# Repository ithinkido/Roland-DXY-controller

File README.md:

# Roland-DXY-controller
 A modern ESP32 based controller for Roland DXY plotter with i2c shift regisers for button mapping, OLED dispay, solenoid drivers and on board TMC silent stepper drivers 

 Two boards have been designed. 
 ## [TMC 2208](https://github.com/ithinkido/Roland-DXY-controller/tree/TMC-2208)
 Standard STEP/DIR  control no UART
 ## [TMC 2209](https://github.com/ithinkido/Roland-DXY-controller/tree/TMC-2209)
  UAURT + STEP/DIR control with posiblity to use stall guard and all other features of UART controlled TMC

  **See branches for more info**

The board is designed to be a a plug in replacemnt with NO modifications to the existing plotter hardware.

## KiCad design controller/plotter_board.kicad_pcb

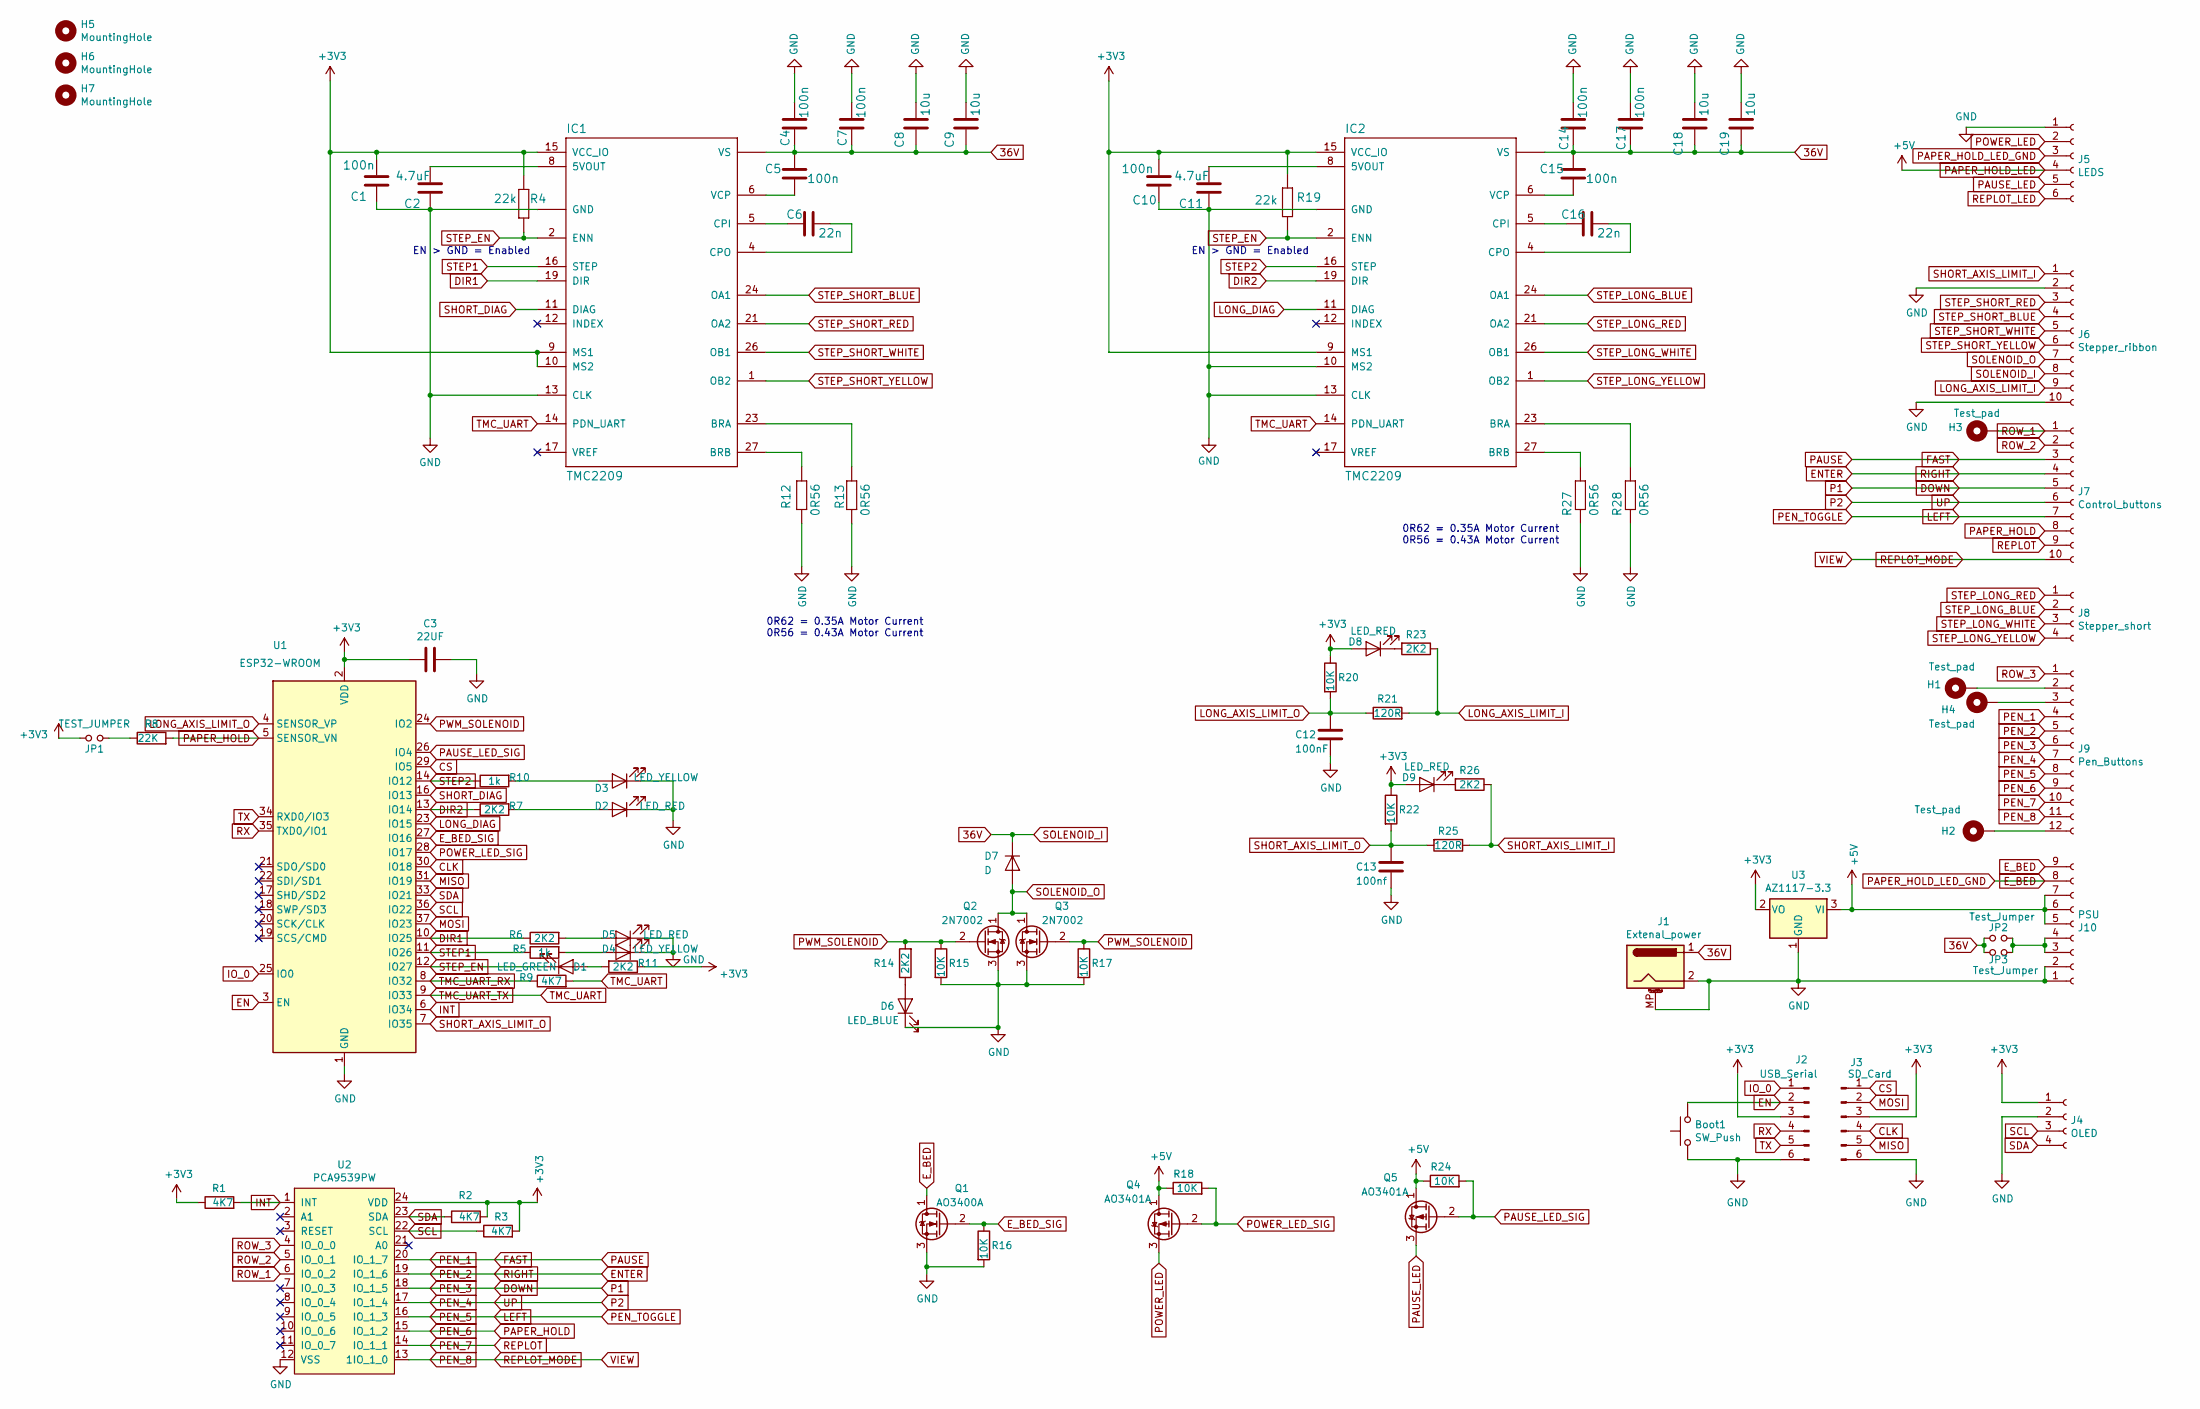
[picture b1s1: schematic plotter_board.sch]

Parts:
Boot1: SW_Push; SW_Tactile_SPST_Angled_PTS645Vx58-2LFS
C1, C5, C10, C15: 100n; C_0402_1005Metric; LCSC C1525
C2, C11: 4.7uF; C_0402_1005Metric; LCSC C23733
C3: 22UF; C_0603_1608Metric; LCSC C59461
C4, C7, C14, C17: 100n; C_0603_1608Metric; LCSC C14663
C6, C16: 22n; C_0402_1005Metric; LCSC C1532
C8, C9, C18, C19: 10u; C_1206_3216Metric; LCSC C13585
C12: 100nF; C_0402_1005Metric; LCSC C1525
C13: 100nf; C_0402_1005Metric; LCSC C1525
D1: LED_GREEN; LED_0603_1608Metric; LCSC C72043
D2, D5, D8, D9: LED_RED; LED_0603_1608Metric; LCSC C2286
D3, D4: LED_YELLOW; LED_0603_1608Metric; LCSC C72038
D6: LED_BLUE; LED_0603_1608Metric; LCSC C72041
D7: D; D_SOD-123F; LCSC C64898
H1, H2, H3, H4: Test_pad; PinHeader_1x01_P2.54mm_Vertical
H5, H6, H7: MountingHole; MountingHole_3.7mm_Pad_Via
IC1, IC2: TMC2209; TMC2209-LA; LCSC C465949
J1: Extenal_power; BarrelJack_Wuerth_6941xx301002
J2: USB_Serial; PinSocket_1x06_P2.54mm_Vertical
J3: SD_Card; PinSocket_1x06_P2.54mm_Vertical
J4: OLED; PinHeader_1x04_P2.54mm_Vertical
J5: LEDS; Molex_SPOX_5267-06A_1x06_P2.50mm_Vertical
J6: Stepper_ribbon; Ribbon_1.25mm_FFC_10pin
J7: Control_buttons; Molex_SPOX_5267-10A_1x10_P2.50mm_Vertical
J8: Stepper_short; PinHeader_1x04_P2.00mm_Vertical
J9: Pen_Buttons; Molex_SPOX_5267-12A_1x12_P2.50mm_Vertical
J10: PSU; Molex_SPOX_5267-09A_1x09_P2.50mm_Vertical
JP1: TEST_JUMPER; SolderJumper-2_P1.3mm_Open_RoundedPad1.0x1.5mm
JP2, JP3: Test_Jumper; SolderJumper-2_P1.3mm_Open_RoundedPad1.0x1.5mm
Q1: AO3400A; SOT-23; LCSC C20917
Q2, Q3: 2N7002; SOT-23; LCSC C8545
Q4, Q5: AO3401A; SOT-23; LCSC C15127
R1: 4K7; R_0402_1005Metric; LCSC C25744
R2, R3, R9: 4K7; R_0402_1005Metric; LCSC C25900
R4, R19: 22k; R_0402_1005Metric; LCSC C25768
R5, R10: 1k; R_0603_1608Metric; LCSC C21190
R6, R7, R11, R14, R23, R26: 2K2; R_0603_1608Metric; LCSC C4190
R8: 22K; R_0402_1005Metric; LCSC C25768
R12, R13, R27, R28: 0R56; R_1206_3216Metric; LCSC C104949
R15, R16, R17, R18, R20, R22, R24: 10K; R_0402_1005Metric; LCSC C25744
R21, R25: 120R; R_0402_1005Metric; LCSC C25079
U1: ESP32-WROOM; ESP32-WROOM-32; LCSC C473012
U2: PCA9539PW; TSSOP-24_4.4x7.8mm_P0.65mm; LCSC C129516
U3: AZ1117-3.3; SOT-223-3_TabPin2

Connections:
36V: C4.1, C5.1, C7.1, C8.1, C9.1, C14.1, C15.1, C17.1, C18.1, C19.1, D7.1 (K), IC1.22 (VS), IC1.28 (VS), IC2.22 (VS), IC2.28 (VS), J1.1, J6.8, JP2.1, JP3.1
+3V3: C1.2, C3.2, C10.2, D8.2 (A), D9.2 (A), IC1.9 (MS1), IC1.10 (MS2), IC1.15 (VCC_IO), IC2.9 (MS1), IC2.15 (VCC_IO), J2.3, J3.3, J4.1, JP1.2, R1.1, R2.2, R3.2, R4.1, R11.1, R19.1, R20.1, R22.1, U1.2 (VDD), U2.24 (VDD), U3.2 (VO)
CLK: J3.4, U1.30 (IO18)
CS: J3.1, U1.29 (IO5)
DIR1: IC1.19 (DIR), R6.1, U1.10 (IO25)
DIR2: IC2.19 (DIR), R7.1, U1.13 (IO14)
DOWN: J7.5, J9.6, U2.18 (IO_1_5)
EN: Boot1.2, J2.2, U1.3 (EN)
ENTER: J7.4, J9.5, U2.19 (IO_1_6)
E_BED: J5.3, J10.8, J10.9, Q1.1 (D)
E_BED_SIG: Q1.2 (G), R16.1, U1.27 (IO16)
FAST: J7.3, J9.4, U2.20 (IO_1_7)
GND: Boot1.1, C1.1, C2.1, C3.1, C4.2, C7.2, C8.2, C9.2, C10.1, C11.1, C12.2, C13.2, C14.2, C17.2, C18.2, C19.2, D2.1 (K), D3.1 (K), D4.1 (K), D5.1 (K), D6.1 (K), IC1.3 (GND), IC1.13 (CLK), IC1.18 (GND), IC1.29, IC1.TP (GND), IC2.3 (GND), IC2.10 (MS2), IC2.13 (CLK), IC2.18 (GND), IC2.29, IC2.TP (GND), J1.2, J1.MP (MountPin), J2.6, J3.6, J4.2, J5.1, J6.2, J6.10, J10.1, J10.2, Q1.3 (S), Q2.3 (S), Q3.3 (S), R12.1, R13.1, R15.2, R16.2, R17.2, R27.1, R28.1, U1.1 (GND), U1.15 (GND), U1.38 (GND), U1.39 (GND), U2.12 (VSS), U3.1 (GND)
INT: R1.2, U1.6 (IO34), U2.1 (INT)
IO_0: J2.1, U1.25 (IO0)
LEFT: J7.7, J9.8, U2.16 (IO_1_3)
LONG_AXIS_LIMIT_I: J6.9, R21.2, R23.1
LONG_AXIS_LIMIT_O: C12.1, R20.2, R21.1, U1.4 (SENSOR_VP)
LONG_DIAG: IC2.11 (DIAG), U1.23 (IO15)
MISO: J3.5, U1.31 (IO19)
MOSI: J3.2, U1.37 (IO23)
unnamed: C2.2, IC1.8 (5VOUT)
unnamed: C5.2, IC1.6 (VCP)
unnamed: C6.1, IC1.5 (CPI)
unnamed: C6.2, IC1.4 (CPO)
unnamed: C11.2, IC2.8 (5VOUT)
unnamed: C15.2, IC2.6 (VCP)
unnamed: C16.1, IC2.5 (CPI)
unnamed: C16.2, IC2.4 (CPO)
unnamed: D1.2 (A), R11.2
unnamed: D2.2 (A), R7.2
unnamed: D3.2 (A), R10.2
unnamed: D4.2 (A), R5.2
unnamed: D5.2 (A), R6.2
unnamed: D6.2 (A), R14.1
unnamed: D8.1 (K), R23.2
unnamed: D9.1 (K), R26.2
unnamed: H1.1, J9.2
unnamed: H2.1, J9.12
unnamed: H4.1, J9.3
unnamed: IC1.23 (BRA), R13.2
unnamed: IC1.27 (BRB), R12.2
unnamed: IC2.23 (BRA), R28.2
unnamed: IC2.27 (BRB), R27.2
unnamed: J10.3, J10.4, JP2.2, JP3.2
unnamed: JP1.1, R8.1
P2: J7.6, J9.7, U2.17 (IO_1_4)
PAPER_HOLD: J7.8, J9.9, R8.2, U1.5 (SENSOR_VN), U2.15 (IO_1_2)
PAPER_HOLD_LED: J5.4, J10.5, J10.6, J10.7, Q4.1 (D), Q5.1 (D), R18.1, R24.1, U3.3 (VI)
PAUSE_LED: J5.5, Q5.3 (S)
PAUSE_LED_SIG: Q5.2 (G), R24.2, U1.26 (IO4)
PEN_7: J7.9, J9.10, U2.14 (IO_1_1)
PEN_8: J7.10, J9.11, U2.13 (1IO_1_0)
POWER_LED: J5.2, Q4.3 (S)
POWER_LED_SIG: Q4.2 (G), R18.2, U1.28 (IO17)
PWM_SOLENOID: Q2.2 (G), Q3.2 (G), R14.2, R15.1, R17.1, U1.24 (IO2)
REPLOT_LED: J5.6
ROW_1: H3.1, J7.1, U2.6 (IO_0_2)
ROW_2: J7.2, U2.5 (IO_0_1)
ROW_3: J9.1, U2.4 (IO_0_0)
RX: J2.4, U1.35 (TXD0/IO1)
SCL: J4.3, R3.1, U1.36 (IO22), U2.22 (SCL)
SDA: J4.4, R2.1, U1.33 (IO21), U2.23 (SDA)
SHORT_AXIS_LIMIT_I: J6.1, R25.1, R26.1
SHORT_AXIS_LIMIT_O: C13.1, R22.2, R25.2, U1.7 (IO35)
SHORT_DIAG: IC1.11 (DIAG), U1.16 (IO13)
SOLENOID_O: D7.2 (A), J6.7, Q2.1 (D), Q3.1 (D)
STEP1: IC1.16 (STEP), R5.1, U1.11 (IO26)
STEP2: IC2.16 (STEP), R10.1, U1.14 (IO12)
STEP_EN: D1.1 (K), IC1.2 (ENN), IC2.2 (ENN), R4.2, R19.2, U1.12 (IO27)
STEP_LONG_BLUE: IC2.24 (OA1), J8.2
STEP_LONG_RED: IC2.21 (OA2), J8.1
STEP_LONG_WHITE: IC2.26 (OB1), J8.3
STEP_LONG_YELLOW: IC2.1 (OB2), J8.4
STEP_SHORT_BLUE: IC1.24 (OA1), J6.4
STEP_SHORT_RED: IC1.21 (OA2), J6.3
STEP_SHORT_WHITE: IC1.26 (OB1), J6.5
STEP_SHORT_YELLOW: IC1.1 (OB2), J6.6
TMC_UART: IC1.14 (PDN_UART), IC2.14 (PDN_UART), R9.2, U1.9 (IO33)
TMC_UART_RX: R9.1, U1.8 (IO32)
TX: J2.5, U1.34 (RXD0/IO3)

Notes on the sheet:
EN > GND = Enabled
0R62 = 0.35A Motor Current 0R56 = 0.43A Motor Current

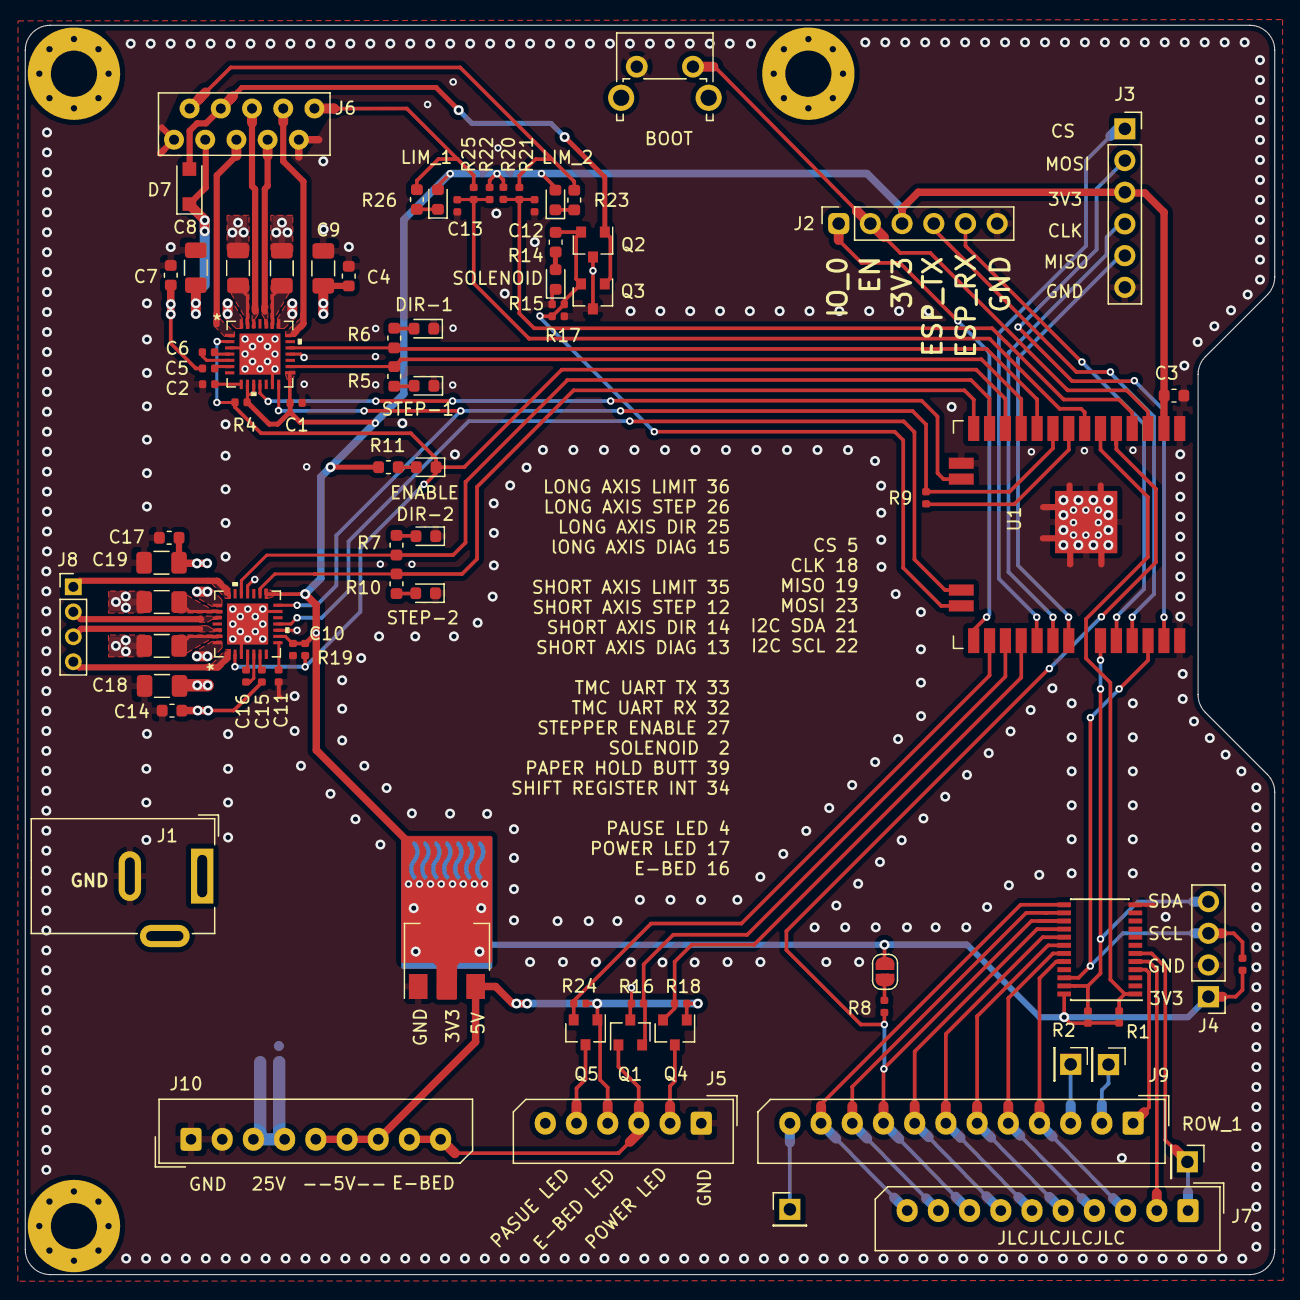
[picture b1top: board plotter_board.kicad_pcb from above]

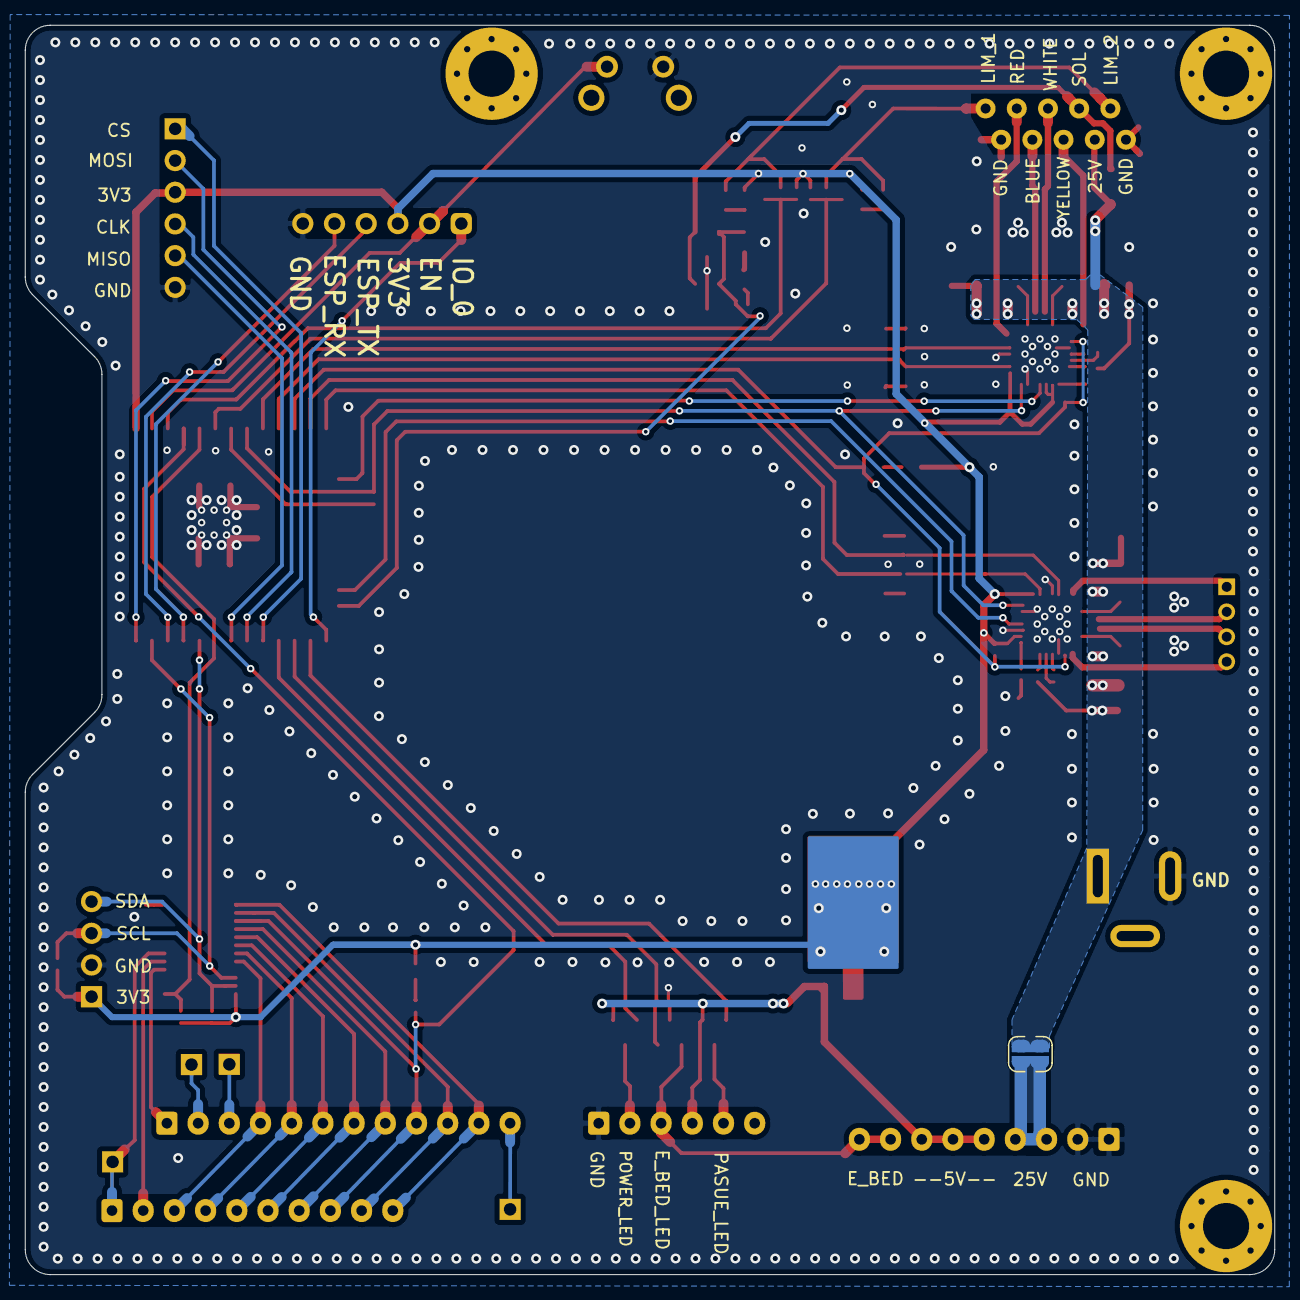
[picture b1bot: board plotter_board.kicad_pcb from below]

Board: 2 copper layers, 100.1 x 100.1 mm, 88 parts (3 on the bottom side), 80 nets.

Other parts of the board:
svg2mod: G***; pad_all

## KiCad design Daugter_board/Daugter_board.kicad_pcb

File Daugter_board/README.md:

This board takes care of the USB-C serial comms as well as the SD card. It is piggybacked onto the main board to postion the connectors correctly within the case openings.

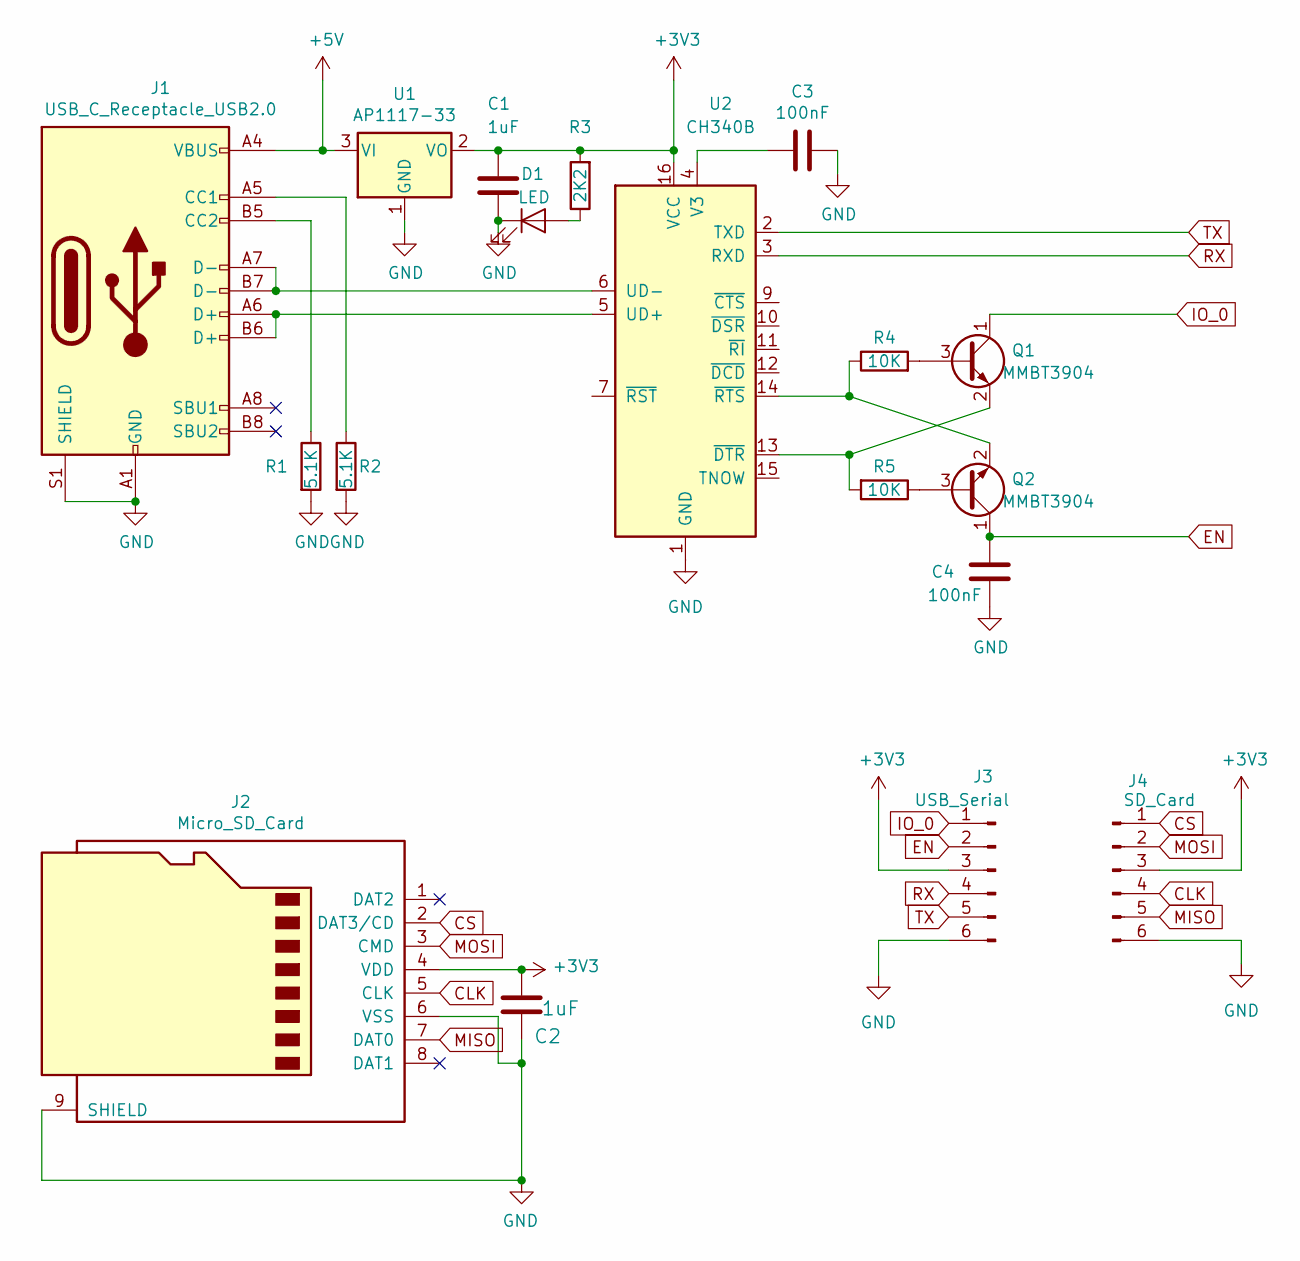
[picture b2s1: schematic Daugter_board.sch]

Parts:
C1: 1uF; C_0402_1005Metric; LCSC C52923
C2: 1uF; C_0805_2012Metric; LCSC C28323
C3, C4: 100nF; C_0402_1005Metric; LCSC C1525
D1: LED; LED_0603_1608Metric; LCSC C72041
J1: USB_C_Receptacle_USB2.0; USB_C_Receptacle_HRO_TYPE-C-31-M-12; LCSC C165948
J2: Micro_SD_Card; Conn_uSDcard; LCSC C111196
J3: USB_Serial; PinSocket_1x06_P2.54mm_Vertical
J4: SD_Card; PinSocket_1x06_P2.54mm_Vertical
Q1, Q2: MMBT3904; SOT-23; LCSC C20526
R1, R2: 5.1K; R_0402_1005Metric; LCSC C25905
R3: 2K2; R_0603_1608Metric; LCSC C4190
R4, R5: 10K; R_0402_1005Metric; LCSC C25744
U1: AP1117-33; SOT-223-3_TabPin2; LCSC C6186
U2: CH340B; SOIC-16_3.9x9.9mm_P1.27mm; LCSC C81010

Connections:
+3V3: C1.1, C2.2, J2.4 (VDD), J3.3, J4.3, R3.2, U1.2 (VO), U2.16 (VCC)
+5V: J1.A4 (VBUS), J1.A9 (VBUS), J1.B4 (VBUS), J1.B9 (VBUS), U1.3 (VI)
CLK: J2.5 (CLK), J4.4
CS: J2.2 (DAT3/CD), J4.1
EN: C4.2, J3.2, Q2.1 (C)
GND: C1.2, C2.1, C3.1, C4.1, D1.1 (K), J1.A1 (GND), J1.A12 (GND), J1.B1 (GND), J1.B12 (GND), J1.S1 (SHIELD), J2.6 (VSS), J2.9 (SHIELD), J3.6, J4.6, R1.2, R2.2, U1.1 (GND), U2.1 (GND)
IO_0: J3.1, Q1.1 (C)
MISO: J2.7 (DAT0), J4.5
MOSI: J2.3 (CMD), J4.2
unnamed: C3.2, U2.4 (V3)
unnamed: D1.2 (A), R3.1
unnamed: J1.A5 (CC1), R2.1
unnamed: J1.A6 (D+), J1.B6 (D+), U2.5 (UD+)
unnamed: J1.A7 (D-), J1.B7 (D-), U2.6 (UD-)
unnamed: J1.B5 (CC2), R1.1
unnamed: Q1.2 (E), R5.2, U2.13 (~DTR)
unnamed: Q1.3 (B), R4.2
unnamed: Q2.2 (E), R4.1, U2.14 (~RTS)
unnamed: Q2.3 (B), R5.1
RX: J3.4, U2.3 (RXD)
TX: J3.5, U2.2 (TXD)

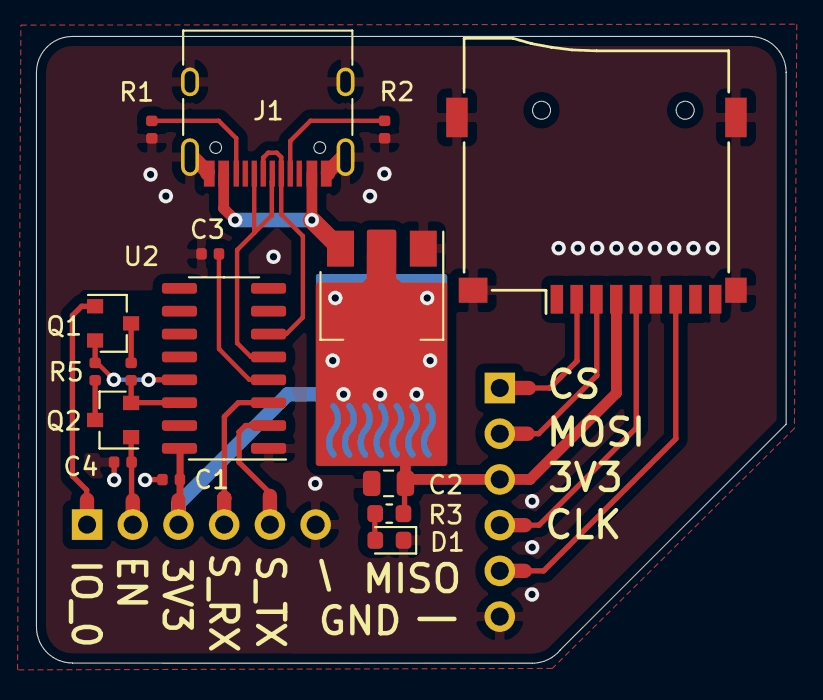
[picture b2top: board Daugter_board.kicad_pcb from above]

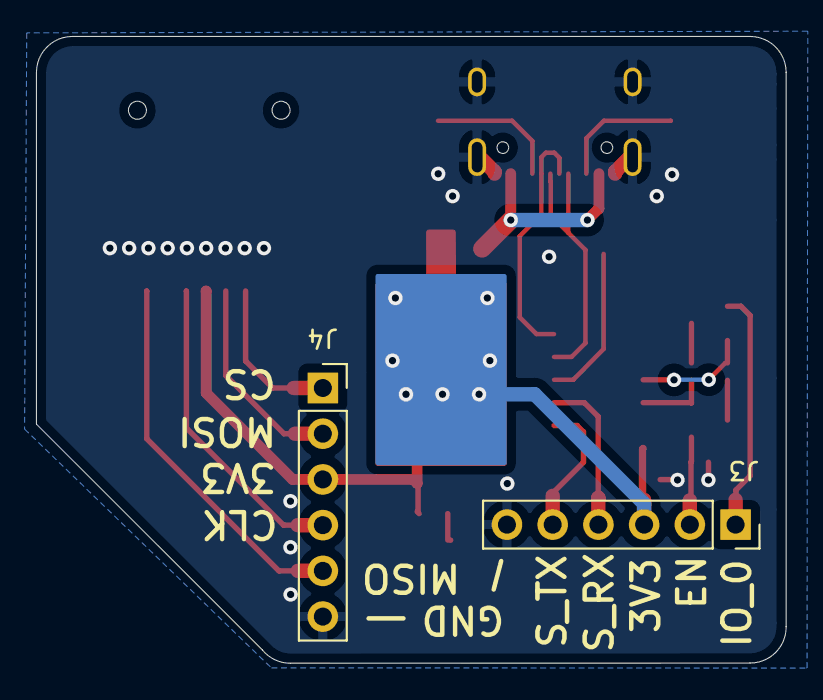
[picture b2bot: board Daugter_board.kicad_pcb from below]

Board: 2 copper layers, 41.7 x 34.8 mm, 19 parts (3 on the bottom side), 21 nets.

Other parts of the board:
svg2mod: G***; pad_all

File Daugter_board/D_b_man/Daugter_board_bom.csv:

Comment,Designator,Footprint,LCSC
"10K","R5,R4","Resistor_SMD:R_0402_1005Metric","C25744"
" MMBT3904","Q1,Q2","Package_TO_SOT_SMD:SOT-23","C20526"
"USB_C_Receptacle_USB2.0","J1","Connector_USB:USB_C_Receptacle_HRO_TYPE-C-31-M-12","C165948"
"5.1K","R2,R1","Resistor_SMD:R_0402_1005Metric","C25905"
"100nf","C4","Capacitor_SMD:C_0402_1005Metric","C1525"
"1uF","C1","Capacitor_SMD:C_0402_1005Metric","C52923"
"Micro_SD_Card","J2","plotter_board:Conn_uSDcard","C111196"
"1uF","C2","Capacitor_SMD:C_0805_2012Metric","C28323"
"AP1117-33","U1","Package_TO_SOT_SMD:SOT-223-3_TabPin2","C6186"
"USB_Serial","J3","Connector_PinSocket_2.54mm:PinSocket_1x06_P2.54mm_Vertical",""
"SD_Card","J4","Connector_PinSocket_2.54mm:PinSocket_1x06_P2.54mm_Vertical",""
"100nF","C3","Capacitor_SMD:C_0402_1005Metric","C1525"
"2K2","R3","Resistor_SMD:R_0603_1608Metric","C4190"
"CH340B","U2","Package_SO:SOIC-16_3.9x9.9mm_P1.27mm","C81010"
"LED","D1","LED_SMD:LED_0603_1608Metric","C72041"

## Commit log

2021-12-08 Upload
2021-12-08 Images
2021-12-08 Fix pin maps
2021-12-12 Upload files
2021-12-12 move to branches
2021-12-12 Crop images
2021-12-12 Better routing
2021-12-12 Better routing.
2021-12-13 Add info to Daughter board
